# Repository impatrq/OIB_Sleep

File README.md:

ORTHOPEDICAL INTELLIGENT BED

INTEGRANTES:
Ezequiel Bourlot
Lorenzo Fernández
Joaquín Vignettta
Federico Domoñi

Objetivo:
Un colchón que se termo regule dependiendo del estado de sueño en el que se encuentre una persona 

Cómo surgió el proyecto?

La idea del proyecto surgio debido a problemas de sueño generales en la familia de un integrante y cuando buscamos estudios descubrimos que son muy comunes y tienen grandes efectos sobre la mayoria de la población y tambien que se podian aliviar con la temperatura durante el sueño

Video presentación:
https://youtu.be/yen7QRbAJQ8?si=tZINnR11tU10LYak

Página Web e instagram:
https://oib-sleep.vercel.app
https://www.instagram.com/oibsleep?igsh=MXVqZHRpbnUxYzlxYw==

Descripción y aplicaciones:
El proyecto cuenta con una férula la cual toma datos biométricos de la persona (ritmo cardiaco, temperatura ambiente, temperatura corporal, acelerómetro) para determinar el estado de sueño en el que se encuentra un a persona. 
De ahí, manda estos datos a unos tanques de agua donde se determinará si se tiene que mandar agua fría o caliente a través del colchón mediante la utilización de caños de cobre.
La idea es poder prolongar el estado de sueño REM de una persona para así mejorar su calidad de sueño. 
También, al regular la temperatura del colchón, se puede tratar distintas patologías en pacientes de hospitales, ya sean personas con problemas de migrañas, adultos mayores con poca termo regulación, personas cuadripléjicas que no pueden determinar la temperatura de su cuerpo, etc.

Agradecimientos: A Simmons, Layer by Layer y la cooperadora de la escuela por proveernos con los materiales para poder llevar acabo el proyecto y la ayuda.

Contactos:

Joaquin Vignetta: jvignetta@gmail.com
https://www.linkedin.com/in/joaquin-vignetta-2a78a7398 
https://github.com/joavig357

Federico Rodriguez Domoñi: federicorodriguezdomoni@gmail.com
https://www.linkedin.com/in/federico-rodriguez-domoñi-6005b51b8
https://github.com/FedericoRD

Ezequiel Bourlot: ezequiel.bourlot@gmail.com
https://www.linkedin.com/in/ezequiel-bourlot-a96094232
https://github.com/eze2508

Lorenzo Fernandez: lfern9407@gmail.com
https://www.linkedin.com/in/maximo-lorenzo-fernandez-39a160397
https://github.com/lorenzrt

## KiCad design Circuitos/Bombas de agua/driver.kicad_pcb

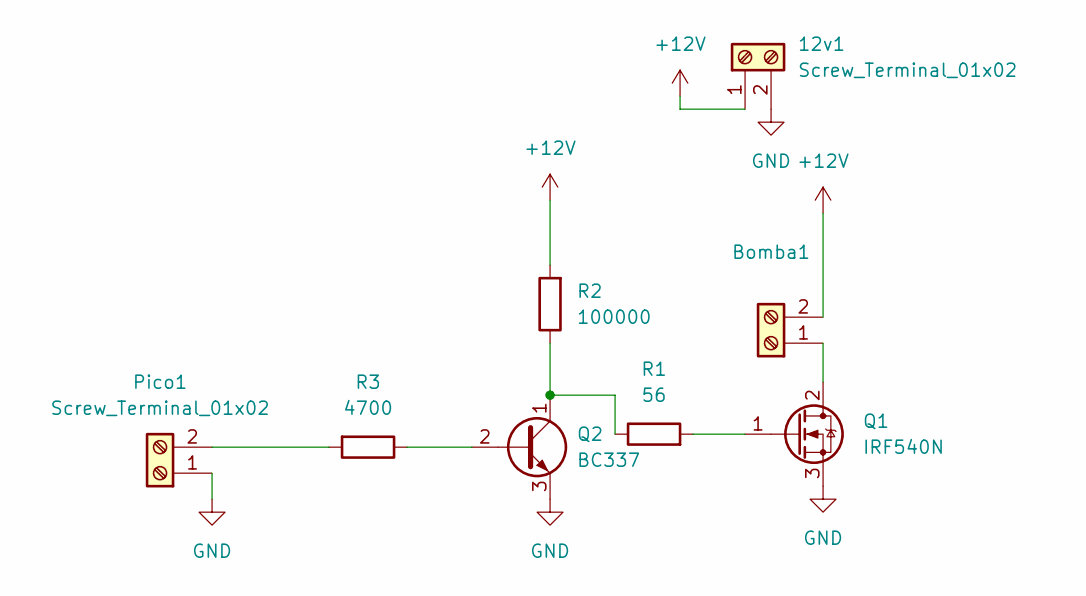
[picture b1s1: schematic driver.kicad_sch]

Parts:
12v1: Screw_Terminal_01x02; TerminalBlock_MaiXu_MX126-5.0-02P_1x02_P5.00mm
Bomba1: Screw_Terminal_01x02; TerminalBlock_MaiXu_MX126-5.0-02P_1x02_P5.00mm
Pico1: Screw_Terminal_01x02; TerminalBlock_MaiXu_MX126-5.0-02P_1x02_P5.00mm
Q1: IRF540N; TO-220-3_Vertical
Q2: BC337; TO-92_Inline
R1: 56; R_Box_L14.0mm_W5.0mm_P9.00mm
R2: 100000; R_Box_L14.0mm_W5.0mm_P9.00mm
R3: 4700; R_Box_L14.0mm_W5.0mm_P9.00mm

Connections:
unnamed: 12v1.1, Bomba1.2, R2.2
unnamed: 12v1.2, Pico1.1, Q1.3 (S), Q2.3 (E)
unnamed: Bomba1.1, Q1.2 (D)
unnamed: Pico1.2, R3.2
unnamed: Q1.1 (G), R1.2
unnamed: Q2.2 (B), R3.1
unnamed: Q2.1 (C), R1.1, R2.1

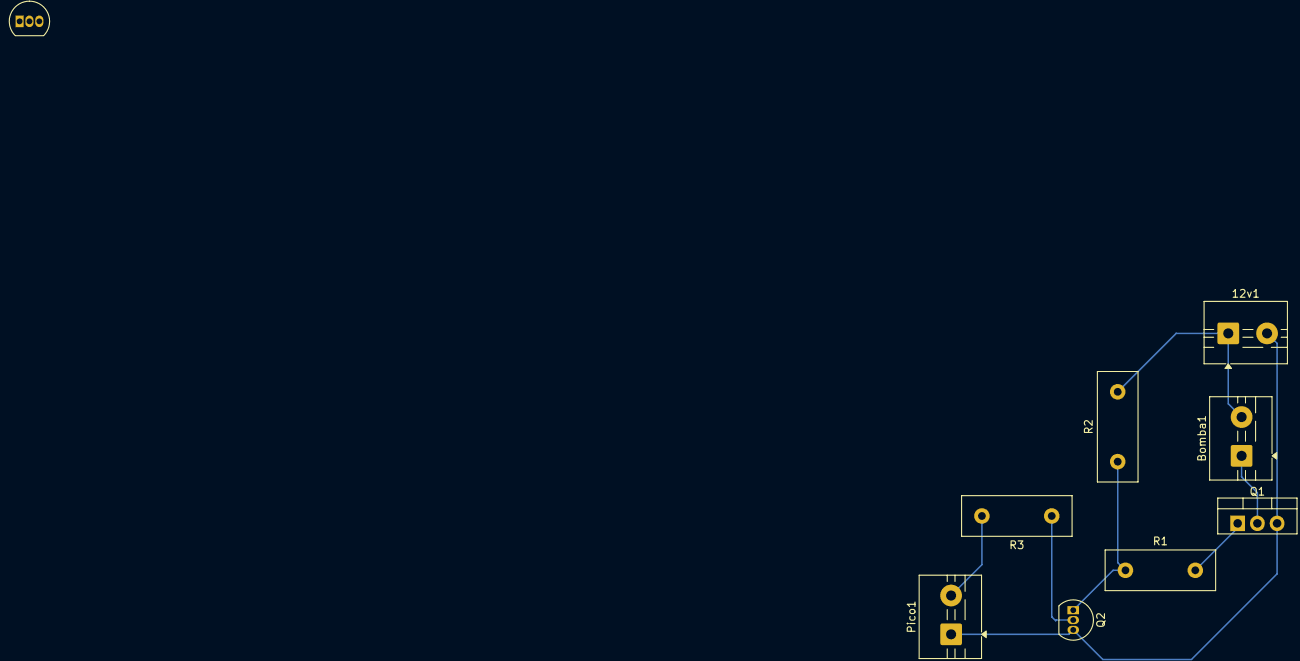
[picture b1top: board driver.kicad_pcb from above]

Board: 2 copper layers, 9 parts (0 on the bottom side), 7 nets.

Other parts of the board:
Q1#2: BS108; TO-92_Inline

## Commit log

2025-07-08 Página Web
    Subo la pagina web de oibsleep
    -Falta agregar fotos
2025-07-08 Update README.md
    se agrego el link de la pagina web al read me
2025-07-08 Create bitacoras
2025-07-14 Subida de Bitacora
2025-07-14 reacomadación
2025-07-14 feat: Agrego diseño de circuito de bombas de agua
    Diseño en kicad del circuito a usar de las bombas de agua
2025-08-28 Rename Bitácora_del_Proyecto_Grupal[1].docx to Documentos/Bitácora_del_Proyecto_Grupal.docx
2025-09-04 Actualizar bitacora
2025-09-23 Create Documentos
2025-10-22 feat: Actualizar Bitacora
    Entradas agregadas de parte de Fede y Vignetta
2025-10-29 algoritmo de sueño
    Agregue el algoritmo sin funcionalidades todavia faltan cambios
2025-10-29 subir el codigo de la pulsera
    andan 2 sensores pero 1 todavia no hace bien el calculo de ritmo cariaco, el sensor de temperatura no es detectado
2025-10-29 carpeta tecnica
    son las 7 primeras paginas hasta ahora, hecha en overleaf
2025-10-29 feat
2025-10-29 feat:borrar manual de usuario
    Error al subir archivo
2025-10-29 feat: Manual de Usuario
    se subió la primera parte del manual de usuario
2025-10-31 feat: Borrar documento Manual de usuario
    Borrar el documento para agregar una version actualizada
2025-10-31 feat: Agregar informacion a Manual de usuario
    Se agrego informacion general y de partes especificas del proyecto
2025-10-31 feat: Agrego versiones de circuito de bombas de agua
2025-10-31 feat: carpeta pulsera
    carpeta para los circuitos de pulsera
2025-10-31 feat: Circuito de pulsera
    Se sube ultima version del circuito de pulsera
2025-10-31 feat: Carpeta de circuitos
    Carpeta para circuitos de resistencia y valvula
2025-10-31 feat: Circuito para control
    Subo circuito para control de resistencia y valvula
2025-10-31 Update Carpeta_Técnica.pdf
    hice de la pagina 9 a la 14
2025-11-01 Delete Documentos/MANUAL DE USUARIO.docx
    Para subir la version actualizada
2025-11-01 feat: Manual de Usuario terminado
    Se termino de completar el manual de usuario
2025-11-01 feat: Video Presentación
    Se termino y subió el video presentación
2025-11-03 Create Cama
2025-11-03 Rename Modelo 3D/0001-0100.mp4 to Modelo 3D/Cama/0001-0100.mp4
2025-11-03 Rename Modelo 3D/CAMA2.blend to Modelo 3D/Cama/CAMA2.blend
2025-11-03 Rename Modelo 3D/bed.glb to Modelo 3D/Cama/bed.glb
2025-11-03 Rename Modelo 3D/0001-0250.mkv to Modelo 3D/Brazalete/0001-0250.mkv
2025-11-03 Rename Modelo 3D/d.blend to Modelo 3D/Brazalete/d.blend
2025-11-03 Rename Modelo 3D/acople.stl to Modelo 3D/Acople/acople.stl
2025-11-03 Rename Modelo 3D/soportes.dwg to Modelo 3D/Soportes de circuitos/soportes.dwg
2025-11-05 feat: Carpeta raspberry
    Se creo la carpeta para la placa de la raspberry pi zero 2 w
2025-11-05 waterController
    Empiezo el codigo defino los pines y los tiempos de las tareas
2025-11-05 sigo con el codigo
    definí todas las tareas
2025-11-05 Historias
    Subí las historias de usuario
2025-11-05 waterController
    determinar el tiempo
2025-11-05 WaterController
    Termine el codigo para mandar agua fria con delays
2025-11-06 feat: Video Presentacion - ACTUALIZADO
    Se subió la versión actualizada del video presentación
2025-11-06 feat: Circuito raspberry actualizado
    Actualizacion de raspberry para ocupar menos espacio
2025-11-06 feat: Actualizacion circuito de raspberry
    Se actualiza el circuito para disminuir el tamaño para que entre
2025-11-06 feat: Bitácora del Proyecto Grupal[1].docx
    Se elimino para actualizar
2025-11-06 feat: Bitacora de Grupo
2025-11-06 feat: Bocetos del Banner
    Bocetos descartados del banner del proyecto
2025-11-06 feat: Banner del Proyecto
    Modelo final del Banner de proyecto
2025-11-06 feat: Banner del Proyecto
    Se subio el banner del proyecto a documentos
2025-11-06 feat: Boceto Banner
    Se subio el Boceto del Banner a Documentos
2025-11-07 Explicacion de presence_detector
2025-11-07 Rename Imagen de WhatsApp 2025-11-06 a las 14.43.27_1ab5a3b6.jpg to boceto.jpg
2025-11-07 Rename Imagen de WhatsApp 2025-11-06 a las 14.43.27_a5c3106a.jpg to texto_boceto.jpg
2025-11-07 Rename Imagen de WhatsApp 2025-11-06 a las 14.43.28_50c6df23.jpg to banner.jpg
2025-11-07 Rename banner.jpg to boceto1.jpg
2025-11-07 Rename boceto.jpg to boceto.jpg
2025-11-07 feat: banner boceto1.jpg
2025-11-07 feat: texto_boceto.jpg
2025-11-07 Carpeta
    actualizacion carpeta tecnica
2025-11-07 explicación analyzer.py
2025-11-07 Rename Modelo 3D/acople 2 .stl to Modelo 3D/Acople/acople 2 .stl
    Acople para la electro válvula
2025-11-07 feat: Bitácora del Proyecto Grupa
    se borro para actualizar
2025-11-07 feat: Bitácora del Proyecto Grupal
    Se actualizo la bitácora
2025-11-07 subir codigo de latex
2025-11-07 feat: Carpeta tecnica
    Se agrego informacion de circuitos a la carpeta tecnica
2025-11-07 carpeta tecnica
    Llegue hasta la pagina 50 para la revision faltan cambiar placeholders y poner fotos de circuitos rotas
2025-11-07 carpeta tecnica
2025-11-10 actualizar carpeta tecnica
    actualize varias cosas
2025-11-10 actualize la carpeta tecnica
    agregue diagramas de bloques y arreglue unos errores
2025-11-12 Carpeta tecnica
    agregue fotos y tambien subi una parte del la seccion de circuito que hice vignetta.
2025-11-12 Carpeta Tecnica
    Termine la carpeta tecnica (sin fotos de los participantes)
2025-11-12 Termine la carpeta tecnica
2025-11-13 waterController
    cambie los pines
2025-11-14 feat: Actualizar bitacora de proyecto
2025-11-18 Actualizacion de la carpeta tecnica
    Agregue las fotos de la carpeta tecnica
2025-11-18 feat: Bitácora del Proyecto Grupal
    Se elimino para actualizar
2025-11-18 feat: Bitácora del Proyecto Grupal
    Se actualizo la bitacora
2025-11-18 ultima foto
2025-11-18 feat: Curriculum vitae
    Se creo la carpeta de Curriculum vitae
2025-11-20 feat: Agrego lista de compras
2025-11-20 feat: agrego redes del grupo
    Redes de instagram y linkedin del proyecto
2025-11-20 feat: agrego linkedin faltante
2025-11-20 feat: Curriculum Vitae
    Carpeta de los curriculums
2025-11-20 feat: Curriculum vitae
    Se guardo en una carpeta
2025-11-20 feat: Delete Curriculum vitae
    se elimino debido a error
2025-11-20 feat: Curriculum Vitae FEDERICO RODRIGUEZ DOMOÑI
    se elimino debido a error
2025-11-20 feat: alcances inconclusos
2025-11-20 feat: Curriculum Vitae
    su subio el curriculum
2025-11-20 feat: Curriculum vitae
    Se actualizo
2025-11-20 feat: Subo CV
2025-11-21 feat: Subo CV the Bourlot
2025-11-25 feat: subo presentacion
2025-11-28 feat: agrego readme
2025-11-28 feat: readme
2025-12-02 subi fotos
